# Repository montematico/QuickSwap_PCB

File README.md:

A prototype PCB developed for my custom HEVO printer,  designed to enable quick-swappable hotends using a DSUB-24 cable

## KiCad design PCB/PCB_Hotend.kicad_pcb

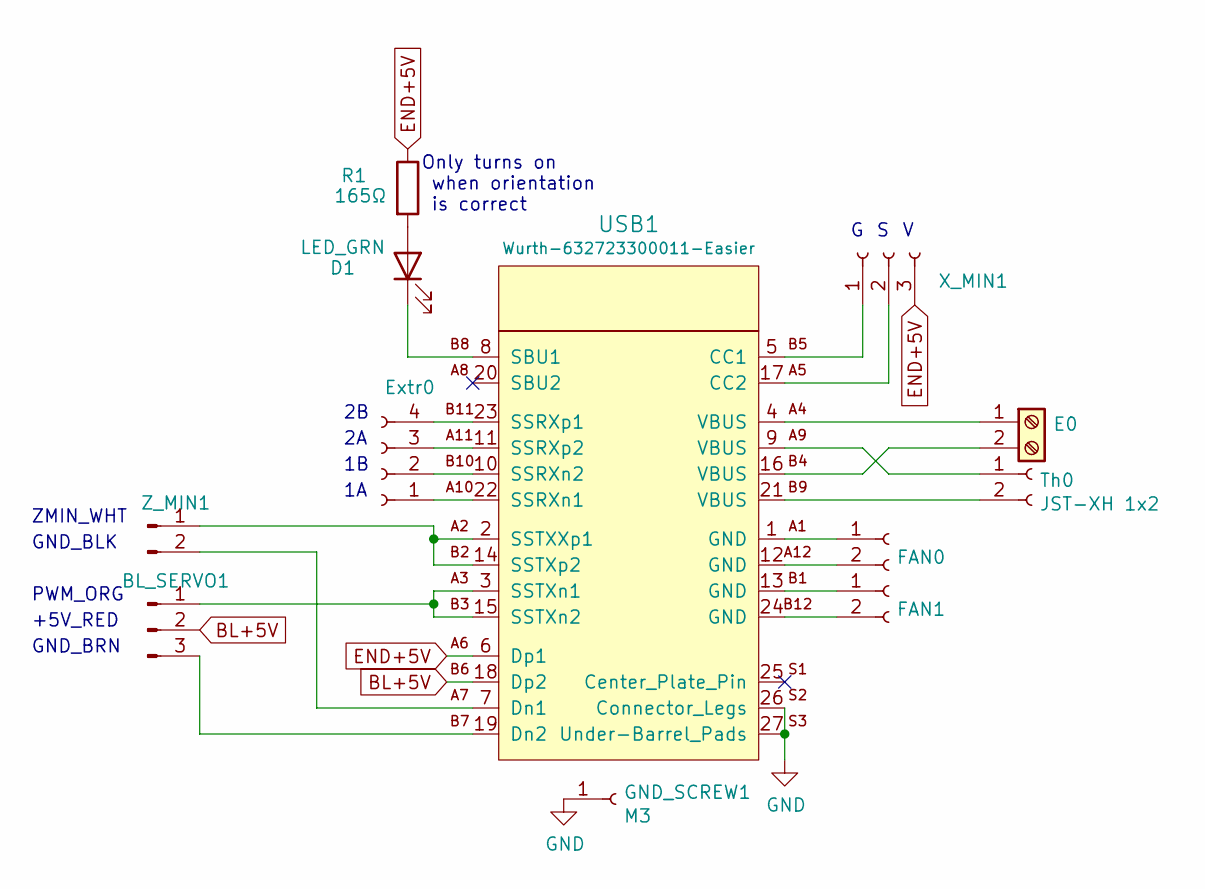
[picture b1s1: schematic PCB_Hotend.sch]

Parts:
BL_SERVO1: BL_SERVO; PinHeader_1x03_P2.54mm_Vertical
D1: LED_GRN; LED_0201_0603Metric
E0: E0; TerminalBlock_Phoenix_MKDS-1,5-2-5.08_1x02_P5.08mm_Horizont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
Extr0: Conn_01x04_Female; JST_XH_B4B-XH-A_1x04_P2.50mm_Vertical
FAN0, FAN1: Conn_01x02_Female; JST_XH_B2B-XH-A_1x02_P2.50mm_Vertical
GND_SCREW1: M3; MountingHole_3.2mm_M3_DIN965_Pad_TopBottom
R1: 165Ω; R_0402_1005Metric_Pad0.72x0.64mm_HandSolder
Th0: JST-XH 1x2; JST_XH_B2B-XH-A_1x02_P2.50mm_Vertical
USB1: Wurth-632723300011-Easier; Wurth-632723300011
X_MIN1: Conn_01x03_Female; JST_XH_B3B-XH-A_1x03_P2.50mm_Vertical
Z_MIN1: Connector_PinHeader_2.54mm:PinHeader_1x02_P2.54mm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; PinHeader_1x02_P2.54mm_Vertical

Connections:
BL+5V: BL_SERVO1.2, USB1.18 (Dp2)
END+5V: R1.1, USB1.6 (Dp1), X_MIN1.3
GND: GND_SCREW1.1, USB1.26 (Connector_Legs), USB1.27 (Under-Barrel_Pads); also elsewhere on the board
unnamed: BL_SERVO1.1, USB1.3 (SSTXn1), USB1.15 (SSTXn2)
unnamed: BL_SERVO1.3, USB1.19 (Dn2)
unnamed: D1.1 (K), USB1.8 (SBU1)
unnamed: D1.2 (A), R1.2
unnamed: E0.1, USB1.4 (VBUS)
unnamed: E0.2, USB1.16 (VBUS)
unnamed: Extr0.1, USB1.22 (SSRXn1)
unnamed: Extr0.2, USB1.10 (SSRXn2)
unnamed: Extr0.3, USB1.11 (SSRXp2)
unnamed: Extr0.4, USB1.23 (SSRXp1)
unnamed: FAN0.1, USB1.1 (GND)
unnamed: FAN0.2, USB1.12 (GND)
unnamed: FAN1.1, USB1.13 (GND)
unnamed: FAN1.2, USB1.24 (GND)
unnamed: Th0.1, USB1.9 (VBUS)
unnamed: Th0.2, USB1.21 (VBUS)
unnamed: USB1.5 (CC1), X_MIN1.1
unnamed: USB1.7 (Dn1), Z_MIN1.2
unnamed: USB1.2 (SSTXXp1), USB1.14 (SSTXp2), Z_MIN1.1
unnamed: USB1.17 (CC2), X_MIN1.2

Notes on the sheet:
Only turns on when orientation is correct
ZMIN_WHT
GND_BLK
PWM_ORG
+5V_RED
GND_BRN

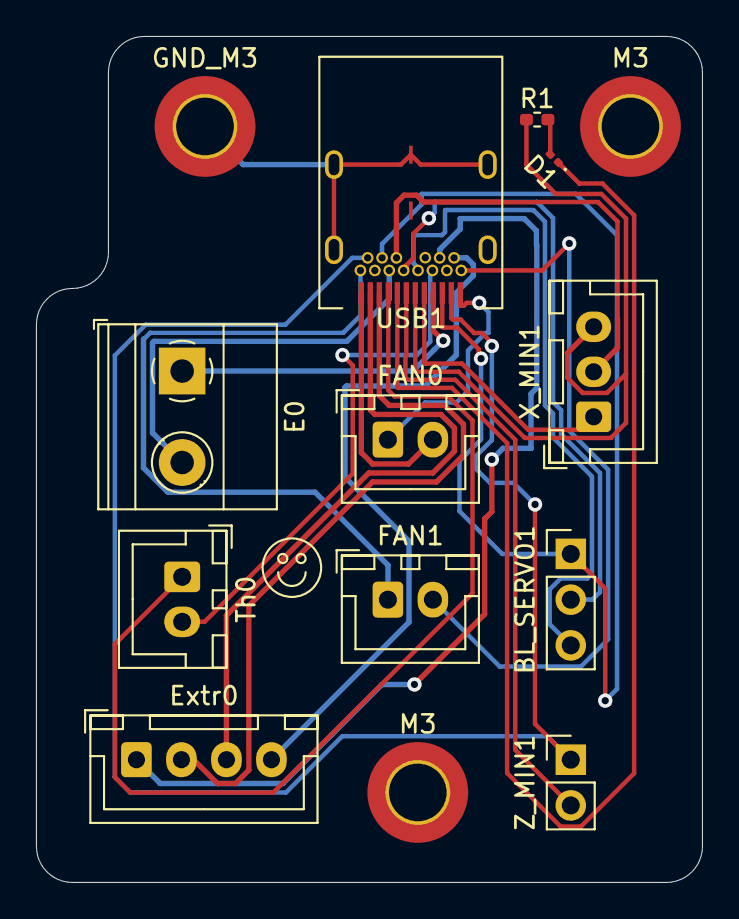
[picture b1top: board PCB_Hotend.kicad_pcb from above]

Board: 2 copper layers, 37.0 x 47.0 mm, 14 parts (0 on the bottom side), 23 nets.

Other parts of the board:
GND_M3: M3; MountingHole_3.2mm_M3_DIN965_Pad_TopBottom
M3, M3#2: MountingHole_3.2mm_M3_DIN965_Pad_TopBottom

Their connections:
GND: GND_M3.1; also elsewhere on the board

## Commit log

2021-02-25 Added V1 using USB-C
